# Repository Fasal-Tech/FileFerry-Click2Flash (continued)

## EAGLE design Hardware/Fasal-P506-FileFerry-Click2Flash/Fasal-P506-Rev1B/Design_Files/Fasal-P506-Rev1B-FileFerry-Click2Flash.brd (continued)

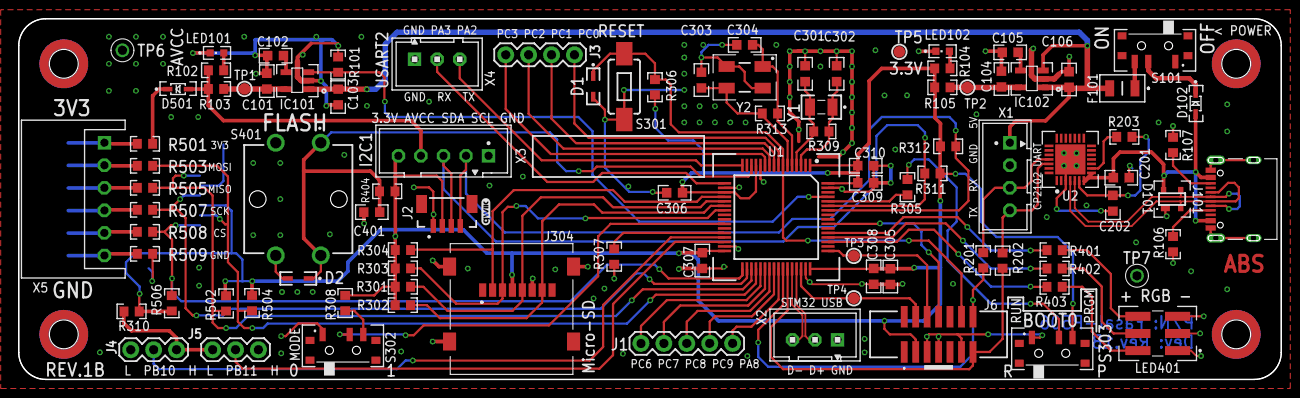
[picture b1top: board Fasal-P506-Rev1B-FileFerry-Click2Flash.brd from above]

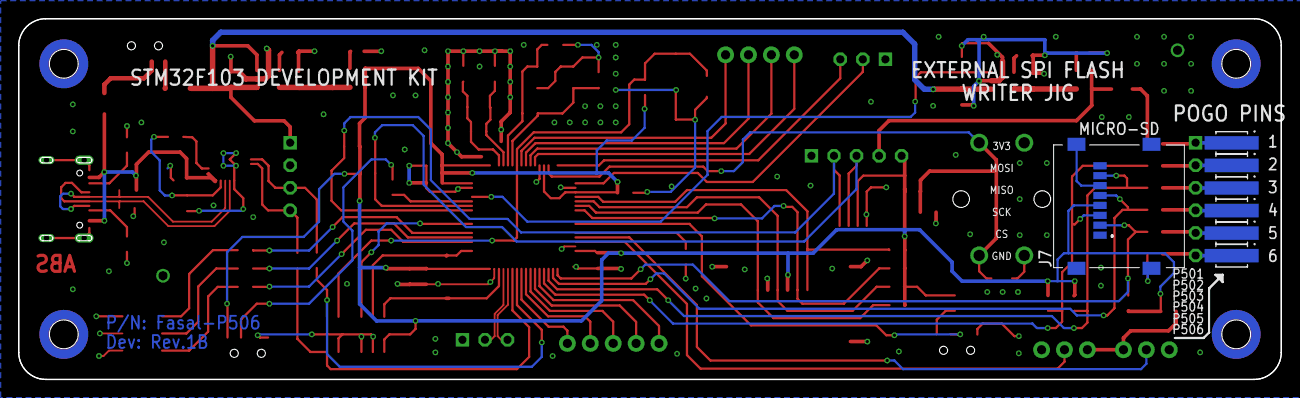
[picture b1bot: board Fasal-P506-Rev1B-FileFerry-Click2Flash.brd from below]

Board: 4 copper layers, 140.0 x 40.0 mm, 103 parts (7 on the bottom side), 77 nets.

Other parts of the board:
U$50: QWIIC_3MM

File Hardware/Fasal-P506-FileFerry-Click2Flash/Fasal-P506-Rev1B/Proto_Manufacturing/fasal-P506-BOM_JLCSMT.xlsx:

Comment | Designator | Footprint | JLCPCB Part #（optional）
1uF | C101, C103, C104, C106 | C0603K | C15849
22nF | C102, C105 | C0603K | C21122
4.7uF | C201, C202 | C0603K | C19666
15pF | C301, C302 | C0603K | C1644
27pF | C303, C304 | C0603K | C107045
100nF | C305, C306, C307, C308, C309, C310, C401 | C0603K | C14663
ESD PESD5V0S1BA | D1, D2 | SOD323 | C19224
ESD PRTR5V0U2X,215 | D101 | PRTR5V0U2X | C2827688
SDM2U20SD3-7 | D102, D501 | SOD-323 | C460258
6V 3A PTC Fuse (Power) | F101 | R1206 | C960021
RT9193-33GB | IC101, IC102 | SOT94P279X130-5N | C15651
USB Type-C data+power | J101 | Surface Mount, Right Angle; Through Hole | C7527694
Sparkfun Qwicc connector Vertical SMD | J2 | 4 pin JST 1mm | C160390
Programming Header SMD 7x2 1.27mm | J6 | 7X2-SMD-1.27MM-SHROUDED | C2881912
Micro SD Card Holder SMD - Flap | J304 | 472192001 | C266609
RED | LED101, LED102 | L0603 | C2286
RGB 5050 | LED401 | 5050 | C3975087
100K | R101 | R0603 | C25803
4.7K | R102, R104 | R0603 | C23162
0E / 0603 | R103, R105, R201, R202, R501, R503, R505, R507, R508, R509 | R0603 | C21189
5.1K | R106, R107 | R0603 | C23186
1K | R203 | R0603 | C21190
10K | R302, R303, R304, R305, R306, R307, R308, R310, R404 | R0603 | C25804
10M | R309 | R0603 | C7250
2.2K | R311, R312 | R0603 | C4190
1M | R313 | R0603 | C105578
100E | R401, R402 | R0603 | C22775
390E | R403 | R0603 | C23151
SWITCH-SPDT-SMD-RIGHT-ANGLE | S101, S302, S303 | SWITCH_SPST_SMD_A | C2890358
TACT SWITCH (Push Button) | S301 | TACTILE_SWITCH_SMD_6.0X3.5MM | C318938
STM32F103RET6 | U1 | 64-LQFP | C8322
CP2102N-A02-GQFN28R | U2 | 28-QFN | C964632
LSE 32.768KHZ 12.5pF, SMD Rectangle 3.20mm x 1.50mm | Y1 | 2-SMD, No Lead | C32346
8MHz Crystal 18pF, Small 4 SMD | Y2 | 5.00mm x 3.20mm | C83312
TACT SWITCH BIG 12x12mm (Push Button) | S401 | TACTILE_SWITCH_THT_12.0x12.0MM | C84931
B4B-XH-A(LF)(SN) PCB connector | X1 | JST Connector B4B-XH-A | C37815
B3B-XH-A(LF)(SN) PCB connector | X2, X4 | JST Connector B3B-XH-A | C2316
B5B-XH-A(LF)(SN) PCB connector | X3 | JST Connector B5B-XH-A | C2318
S6B-XH-A(LF)(SN) R/A PCB connector | X5 | JST Connector S6B-XH-A | C157919

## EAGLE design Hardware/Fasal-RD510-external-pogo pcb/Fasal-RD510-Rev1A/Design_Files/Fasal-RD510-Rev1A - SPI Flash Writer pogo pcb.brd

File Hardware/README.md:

FileFerry-Click2Flash - Hardware
========================================
This directory will contain the hardware design files for the 'FileFerry-Click2Flash project.

# ECAD Tool #
Autodesk Eagle 9.6.2

# Repository Contents #
* **/Fasal-P506-Rev1B-SPI_Flash_Writer_Jig** - All Eagle design files and manufacturing files for the main product "FileFerry-Click2Flash" (.brd, .sch)
* **/Fasal-RD510 - SPI Flash Writer pogo pcb** - Eagle design files and manufacturing files for optional pogo pin PCB to create a test jig

# Hardware Bloack Diagram

## Contact-Me

- <abhaysbharadwaj@gmail.com> over E-Mail
- [Abhay S Bharadwaj](https://www.linkedin.com/in/abhaysbharadwaj/) over LinkedIn

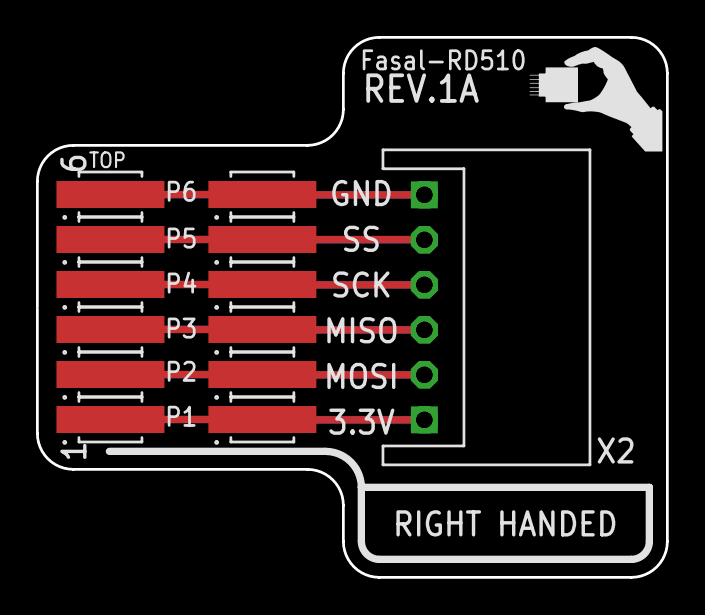
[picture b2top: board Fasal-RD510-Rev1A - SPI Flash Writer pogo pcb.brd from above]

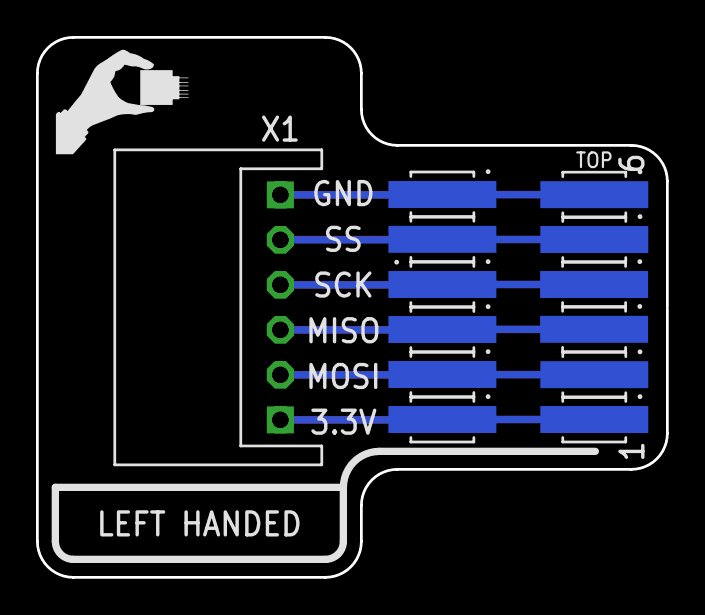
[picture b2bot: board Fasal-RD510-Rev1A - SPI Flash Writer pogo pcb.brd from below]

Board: 2 copper layers, 35.0 x 30.0 mm, 26 parts (13 on the bottom side), 6 nets.

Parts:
P1, P2, P3, P4, P5, P6, P7, P8, P9, P10, P11, P12, P13, P14, P15, P16, P17, P18, P501, P502, P503, P504, P505, P506: RA 1 pin; 1X01_SMD_PAD
X1, X2: S6B-XH-A

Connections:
TP-AVCC: P1.1, P7.1, P13.1, P501.1, X1.1, X2.1
TP-GND: P6.1, P12.1, P18.1, P506.1, X1.6, X2.6
TP-MISO: P3.1, P9.1, P15.1, P503.1, X1.3, X2.3
TP-MOSI: P2.1, P8.1, P14.1, P502.1, X1.2, X2.2
TP-SCK: P4.1, P10.1, P16.1, P504.1, X1.4, X2.4
TP-SS: P5.1, P11.1, P17.1, P505.1, X1.5, X2.5

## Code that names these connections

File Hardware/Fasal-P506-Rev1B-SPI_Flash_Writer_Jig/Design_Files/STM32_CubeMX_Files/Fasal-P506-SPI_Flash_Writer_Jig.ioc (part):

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Mcu.Name=STM32F103R(C-D-E)Tx
Mcu.Package=LQFP64
Mcu.UserName=STM32F103RETx
PA0-WKUP.GPIOParameters=GPIO_Label
PA0-WKUP.GPIO_Label=FLASH_BUTTON
PA0-WKUP.Signal=GPXTI0
PA10.Mode=Asynchronous
PA10.Signal=USART1_RX
PA11.Mode=Device
PA11.Signal=USB_DM
PA12.Mode=Device
PA12.Signal=USB_DP
PA13.Mode=Serial_Wire
PA13.Signal=SYS_JTMS-SWDIO
PA14.Mode=Serial_Wire
PA14.Signal=SYS_JTCK-SWCLK
PA2.Mode=Asynchronous
PA2.Signal=USART2_TX
PA3.Mode=Asynchronous
PA3.Signal=USART2_RX
PA4.Mode=NSS_Signal_Hard_Output
PA4.Signal=SPI1_NSS
PA5.Mode=Full_Duplex_Master
PA5.Signal=SPI1_SCK
PA6.Mode=Full_Duplex_Master
PA6.Signal=SPI1_MISO
PA7.Mode=Full_Duplex_Master
PA7.Signal=SPI1_MOSI
PA9.Mode=Asynchronous
PA9.Signal=USART1_TX
PB0.GPIOParameters=GPIO_Label
PB0.GPIO_Label=QA_MODE
PB0.Signal=GPIO_Input
PB10.GPIOParameters=GPIO_Label
PB10.GPIO_Label=SETTING_GPIO1
PB10.Signal=GPIO_Input
PB11.GPIOParameters=GPIO_Label
PB11.GPIO_Label=SETTING_GPIO2
PB11.Signal=GPIO_Input
PB12.Mode=NSS_Signal_Hard_Output
PB12.Signal=SPI2_NSS
PB13.Mode=Full_Duplex_Master
PB13.Signal=SPI2_SCK
PB14.Mode=Full_Duplex_Master
PB14.Signal=SPI2_MISO
PB15.Mode=Full_Duplex_Master
PB15.Signal=SPI2_MOSI
PB2.GPIOParameters=GPIO_Label
PB2.GPIO_Label=BOOT1
PB2.Signal=GPIO_Input
PB3.GPIOParameters=GPIO_Label
PB3.GPIO_Label=LDE_RED
PB3.Signal=GPIO_Output
PB4.GPIOParameters=GPIO_Label
PB4.GPIO_Label=LED_BLUE
PB4.Signal=GPIO_Output
PB5.GPIOParameters=GPIO_Label
PB5.GPIO_Label=LED_GREEN
PB5.Signal=GPIO_Output
PB6.Mode=I2C
PB6.Signal=I2C1_SCL
PB7.Mode=I2C
PB7.Signal=I2C1_SDA
PB8.GPIOParameters=GPIO_Label
PB8.GPIO_Label=AVCC_ENABLE
PB8.Signal=GPIO_Output
PC13-TAMPER-RTC.Mode=Tamper
PC13-TAMPER-RTC.Signal=RTC_TAMPER
PC14-OSC32_IN.Mode=LSE-External-Oscillator
PC14-OSC32_IN.Signal=RCC_OSC32_IN
PC15-OSC32_OUT.Mode=LSE-External-Oscillator
PC15-OSC32_OUT.Signal=RCC_OSC32_OUT
PD0-OSC_IN.Mode=HSE-External-Oscillator
PD0-OSC_IN.Signal=RCC_OSC_IN
PD1-OSC_OUT.Mode=HSE-External-Oscillator
PD1-OSC_OUT.Signal=RCC_OSC_OUT
RCC.SYSCLKFreq_VALUE=48000000
RCC.SYSCLKSource=RCC_SYSCLKSOURCE_PLLCLK
board=custom

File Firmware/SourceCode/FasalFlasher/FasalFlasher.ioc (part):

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Mcu.Name=STM32F103R(C-D-E)Tx
Mcu.Package=LQFP64
Mcu.UserName=STM32F103RETx
PA0-WKUP.GPIOParameters=GPIO_Label
PA0-WKUP.GPIO_Label=FLASH_BUTTON
PA0-WKUP.Signal=GPXTI0
PA10.Mode=Asynchronous
PA10.Signal=USART1_RX
PA13.Mode=Serial_Wire
PA13.Signal=SYS_JTMS-SWDIO
PA14.Mode=Serial_Wire
PA14.Signal=SYS_JTCK-SWCLK
PA2.Mode=Asynchronous
PA2.Signal=USART2_TX
PA3.Mode=Asynchronous
PA3.Signal=USART2_RX
PA4.GPIOParameters=GPIO_Label
PA4.GPIO_Label=SPI1_NSS
PA4.Signal=GPIO_Output
PA5.Mode=Full_Duplex_Master
PA5.Signal=SPI1_SCK
PA6.Mode=Full_Duplex_Master
PA6.Signal=SPI1_MISO
PA7.Mode=Full_Duplex_Master
PA7.Signal=SPI1_MOSI
PA9.Mode=Asynchronous
PA9.Signal=USART1_TX
PB0.GPIOParameters=GPIO_Label
PB0.GPIO_Label=TRANSFER_MODE
PB0.Signal=GPIO_Input
PB10.GPIOParameters=GPIO_Label
PB10.GPIO_Label=SETTING_GPIO1
PB10.Signal=GPIO_Input
PB11.GPIOParameters=GPIO_Label
PB11.GPIO_Label=SETTING_GPIO2
PB11.Signal=GPIO_Input
PB12.GPIOParameters=GPIO_Label
PB12.GPIO_Label=SPI2_NSS
PB12.Signal=GPIO_Output
PB13.Mode=Full_Duplex_Master
PB13.Signal=SPI2_SCK
PB14.Mode=Full_Duplex_Master
PB14.Signal=SPI2_MISO
PB15.Mode=Full_Duplex_Master
PB15.Signal=SPI2_MOSI
PB2.GPIOParameters=GPIO_Label
PB2.GPIO_Label=BOOT1
PB2.Signal=GPIO_Input
PB3.GPIOParameters=GPIO_Label
PB3.GPIO_Label=LED_G1
PB3.Signal=GPIO_Output
PB4.GPIOParameters=GPIO_Label
PB4.GPIO_Label=LED_B1
PB4.Signal=GPIO_Output
PB5.GPIOParameters=GPIO_Label
PB5.GPIO_Label=LED_R1
PB5.Signal=GPIO_Output
PB6.Mode=I2C
PB6.Signal=I2C1_SCL
PB7.Mode=I2C
PB7.Signal=I2C1_SDA
PB8.GPIOParameters=GPIO_Label
PB8.GPIO_Label=SENSOR_POWER_ENABLE
PB8.Signal=GPIO_Output
PC10.GPIOParameters=GPIO_Label
PC10.GPIO_Label=LED_B
PC10.Signal=GPIO_Output
PC11.GPIOParameters=GPIO_Label
PC11.GPIO_Label=LED_R
PC11.Signal=GPIO_Output
PC12.GPIOParameters=GPIO_Label
PC12.GPIO_Label=LED_G
PC12.Signal=GPIO_Output
PC13-TAMPER-RTC.Mode=Tamper
PC13-TAMPER-RTC.Signal=RTC_TAMPER
PC14-OSC32_IN.Mode=LSE-External-Oscillator
PC14-OSC32_IN.Signal=RCC_OSC32_IN
PC15-OSC32_OUT.Mode=LSE-External-Oscillator
PC15-OSC32_OUT.Signal=RCC_OSC32_OUT
PD0-OSC_IN.Mode=HSE-External-Oscillator
PD0-OSC_IN.Signal=RCC_OSC_IN
PD1-OSC_OUT.Mode=HSE-External-Oscillator
PD1-OSC_OUT.Signal=RCC_OSC_OUT
RCC.SYSCLKFreq_VALUE=72000000
RCC.SYSCLKSource=RCC_SYSCLKSOURCE_PLLCLK
board=custom

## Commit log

2024-08-08 Update LICENSE
2024-08-08 Hardware design files added
2024-08-08 added hardware design files
    Hardware design files added
2024-08-08 added readme
    added readme
2024-08-08 *Done* 1. Initial commit of Firmware source code and documents
2024-08-08 *Done* 1. Test commit with minor readMe update
2024-08-08 *Done* 1. Added PR1.0 deliverables to version control
2024-08-09 added image assets
2024-08-09 image asset added
2024-08-09 directory restructure
2024-08-09 directory restructure and BOM update
2024-08-09 design update
2024-08-09 assets added
2024-08-09 demo directory added
2024-08-09 *Done* 1. Updated ReadMe under Firmware subfolder
2024-08-09 *Done* 1. Added Demo section to version control
2024-08-09 *Done* 1. Minor clean up of root level project readMe
2024-08-11 Added board bring-up code
2024-08-11 block diagram added
2024-08-11 schematic pdf update
2024-08-11 Gerber update
2024-12-06 * build: 1. Code updated to V1.1 2. Migrated from Cube HAL version V1.8.5 to V1.8.6 3. Added clang formatter and Auto doc generation scripts to codeBase
    feat:
    1. SoftTimer module enhanced to automatically compute overflow time based on clock configuration
    fix:
    1. Improved log messages during setup failure conditions
    style:
    1. Ran clang formatter over User files
2024-12-06 docs: 1. Updated readMe and LL documentation
2024-12-06 docs: 1. ReadMe fixed
2024-12-06 docs: 1. Regenerated LL documentation based on updated ReadMe
